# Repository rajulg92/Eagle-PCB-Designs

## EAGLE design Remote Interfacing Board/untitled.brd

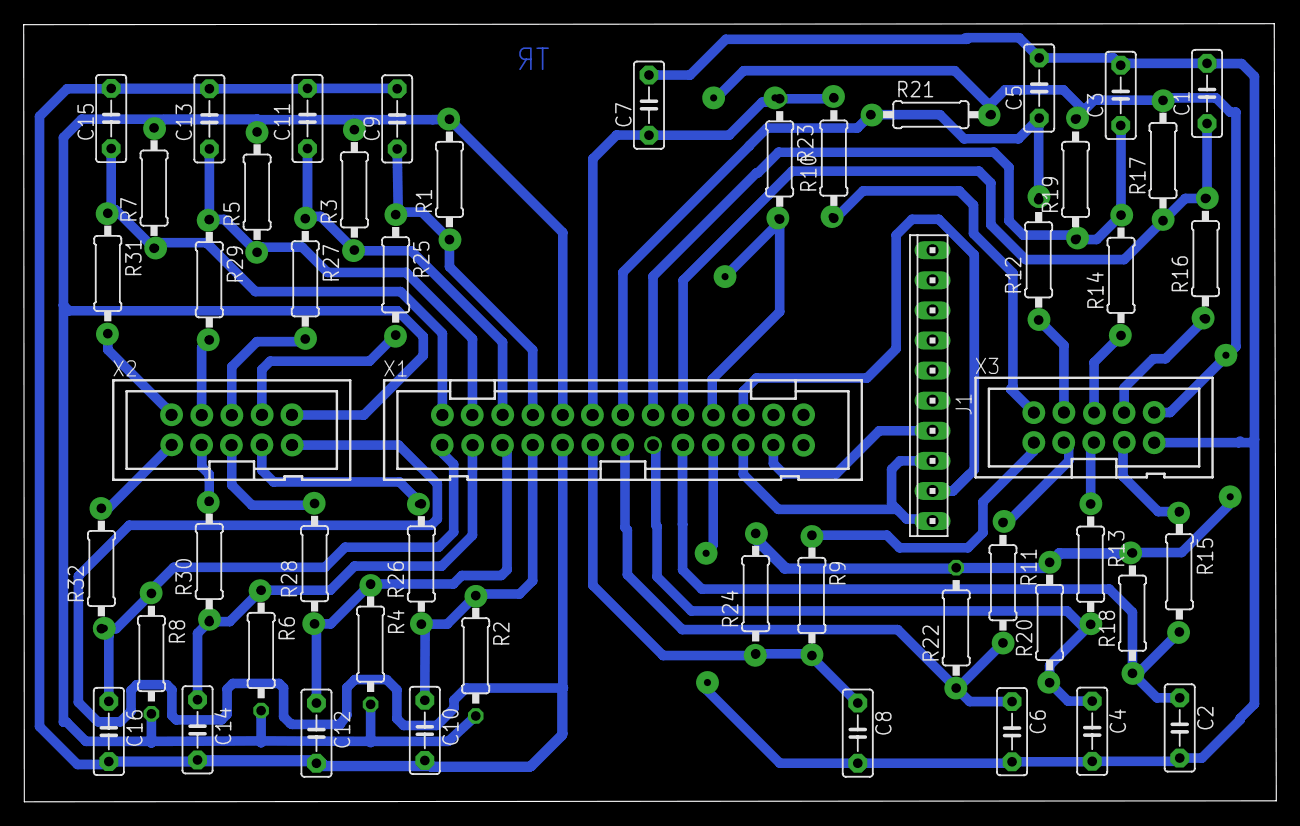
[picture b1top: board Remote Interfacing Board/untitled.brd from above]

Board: 2 copper layers, 105.7 x 65.7 mm, 52 parts (0 on the bottom side), 39 nets.

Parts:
C1, C2, C3, C4, C5, C6, C7, C8, C9, C10, C11, C12, C13, C14, C15, C16: C5B2.5
J1: 10X10MTA
R1, R2, R3, R4, R5, R6, R7, R8, R9, R10, R11, R12, R13, R14, R15, R16, R17, R18, R19, R20, R21, R22, R23, R24, R25, R26, R27, R28, R29, R30, R31, R32: 0207/10
X1: 2526-; PAK100/2500-26
X2, X3: 2510-; PAK100/2500-10

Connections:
unnamed: R32.2, X2.1
unnamed: R31.2, X2.2
unnamed: R30.2, X2.3
unnamed: R29.2, X2.4
unnamed: R28.2, X2.5
unnamed: R27.2, X2.6
unnamed: R26.2, X2.7
unnamed: R25.2, X2.8
unnamed: C16.1, R8.1, R32.1, X1.1
unnamed: C1.1, R16.2, R17.1, X1.18
unnamed: C2.1, R15.2, R18.1, X1.17
unnamed: R9.1, X3.1
unnamed: R10.1, X3.2
unnamed: R11.1, X3.3
unnamed: R12.1, X3.4
unnamed: R13.1, X3.5
unnamed: R14.1, X3.6
unnamed: R15.1, X3.7
unnamed: J1.8, J1.10, X1.21
unnamed: J1.9, X1.22
unnamed: J1.7, X1.23
unnamed: R16.1, X3.8
unnamed: C3.1, R14.2, R19.1, X1.16
unnamed: C4.1, R13.2, R20.1, X1.15
unnamed: C5.1, R12.2, R21.1, X1.14
unnamed: C6.1, R11.2, R22.1, X1.13
unnamed: C7.1, R10.2, R23.1, X1.12
unnamed: C8.1, R9.2, R24.1, X1.11
unnamed: R17.2, R18.2, R19.2, R20.2, R21.2, R22.2, R23.2, R24.2, X1.20, X3.10
unnamed: C1.2, C2.2, C3.2, C4.2, C5.2, C6.2, C7.2, C8.2, X1.19, X3.9
unnamed: C15.1, R7.1, R31.1, X1.2
unnamed: C14.1, R6.1, R30.1, X1.3
unnamed: C13.1, R5.1, R29.1, X1.4
unnamed: C12.1, R4.1, R28.1, X1.5
unnamed: C11.1, R3.1, R27.1, X1.6
unnamed: C10.1, R2.1, R26.1, X1.7
unnamed: C9.1, R1.1, R25.1, X1.8
unnamed: R1.2, R2.2, R3.2, R4.2, R5.2, R6.2, R7.2, R8.2, X1.10, X2.10
unnamed: C9.2, C10.2, C11.2, C12.2, C13.2, C14.2, C15.2, C16.2, X1.9, X2.9

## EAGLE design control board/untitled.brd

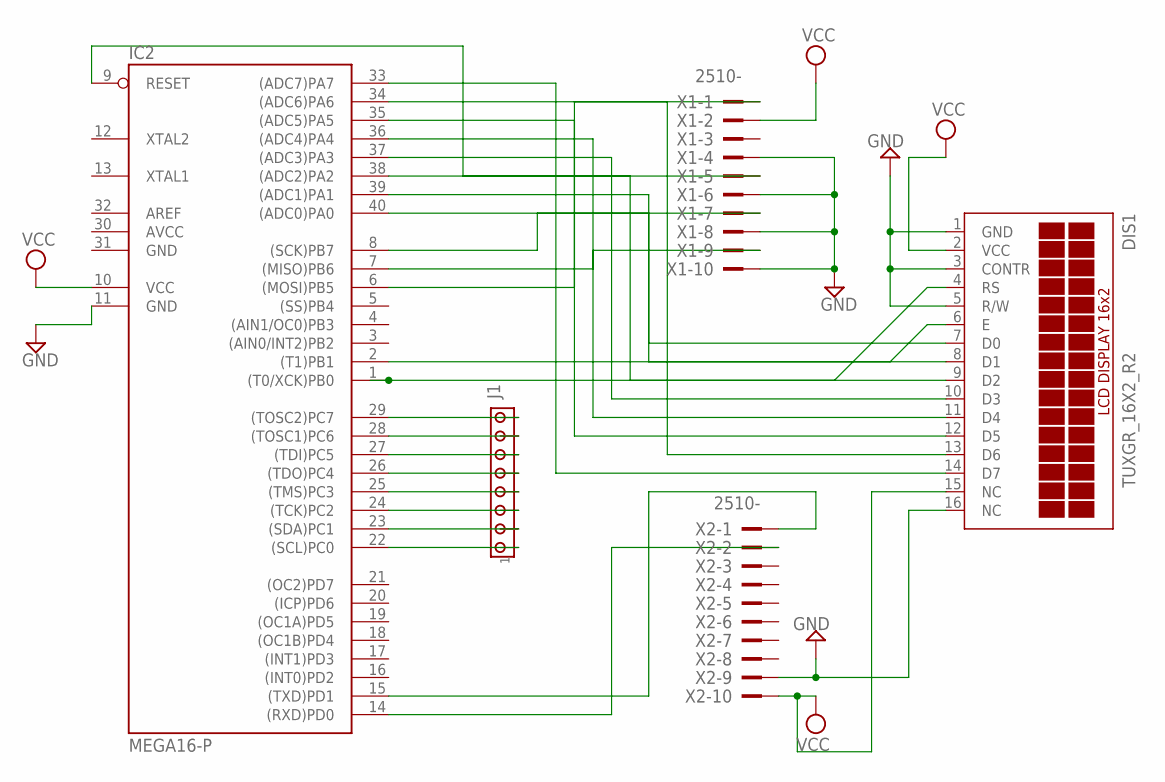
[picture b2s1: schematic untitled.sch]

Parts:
DIS1: TUXGR_16X2_R2
IC2: MEGA16-P; DIL40
J1: MTA08-100; 10X08MTA
X1, X2: 2510-; PAK100/2500-10

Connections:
AVCC: IC2.30 (AVCC)
GND: DIS1.1 (GND), DIS1.3 (CONTR), DIS1.5 (R/W), DIS1.16 (NC), IC2.11 (GND), IC2.31 (GND), X1.4, X1.6, X1.8, X1.10, X2.9
unnamed: IC2.15 ((TXD)PD1), X2.1
unnamed: IC2.14 ((RXD)PD0), X2.2
unnamed: IC2.6 ((MOSI)PB5), X1.1
unnamed: IC2.7 ((MISO)PB6), X1.9
unnamed: IC2.8 ((SCK)PB7), X1.7
unnamed: IC2.9 (RESET), X1.5
unnamed: DIS1.7 (D0), IC2.40 ((ADC0)PA0)
unnamed: IC2.22 ((SCL)PC0), J1.1
unnamed: IC2.23 ((SDA)PC1), J1.2
unnamed: IC2.24 ((TCK)PC2), J1.3
unnamed: IC2.25 ((TMS)PC3), J1.4
unnamed: IC2.26 ((TDO)PC4), J1.5
unnamed: IC2.27 ((TDI)PC5), J1.6
unnamed: IC2.28 ((TOSC1)PC6), J1.7
unnamed: IC2.29 ((TOSC2)PC7), J1.8
unnamed: DIS1.8 (D1), IC2.39 ((ADC1)PA1)
unnamed: DIS1.9 (D2), IC2.38 ((ADC2)PA2)
unnamed: DIS1.10 (D3), IC2.37 ((ADC3)PA3)
unnamed: DIS1.11 (D4), IC2.36 ((ADC4)PA4)
unnamed: DIS1.12 (D5), IC2.35 ((ADC5)PA5)
unnamed: DIS1.13 (D6), IC2.34 ((ADC6)PA6)
unnamed: DIS1.14 (D7), IC2.33 ((ADC7)PA7)
unnamed: DIS1.4 (RS), IC2.1 ((T0/XCK)PB0)
unnamed: DIS1.6 (E), IC2.2 ((T1)PB1)
VCC: DIS1.2 (VCC), DIS1.15 (NC), IC2.10 (VCC), X1.2, X2.10

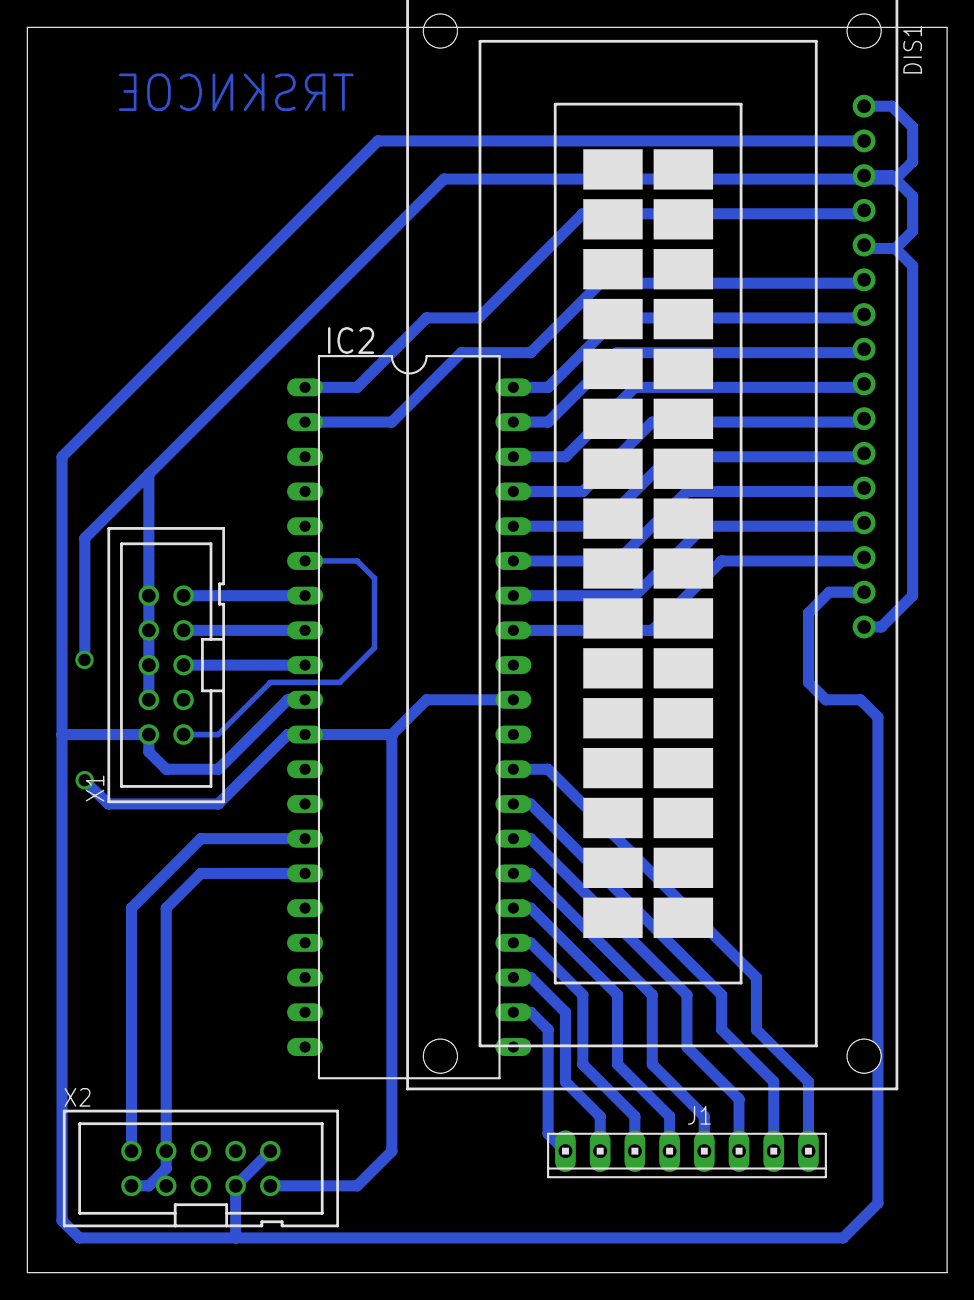
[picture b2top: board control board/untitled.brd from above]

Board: 2 copper layers, 67.3 x 91.1 mm, 5 parts (0 on the bottom side), 26 nets.
